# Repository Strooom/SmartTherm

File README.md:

# SmartTherm
Controlling a Junkers heating (Eurostar ZWE24) with an IoT thermostat

* schematics (kiCAD)
* PCB (kiCAD)
* TouchScreen control (Nextion display)
* SmartPhone app (Blynk)
* 3D Printed enclosure (Fusion360)
* Alternative config with ESPHome and Home Assistant

All documentation is in the Wiki : https://github.com/Strooom/SmartTherm/wiki

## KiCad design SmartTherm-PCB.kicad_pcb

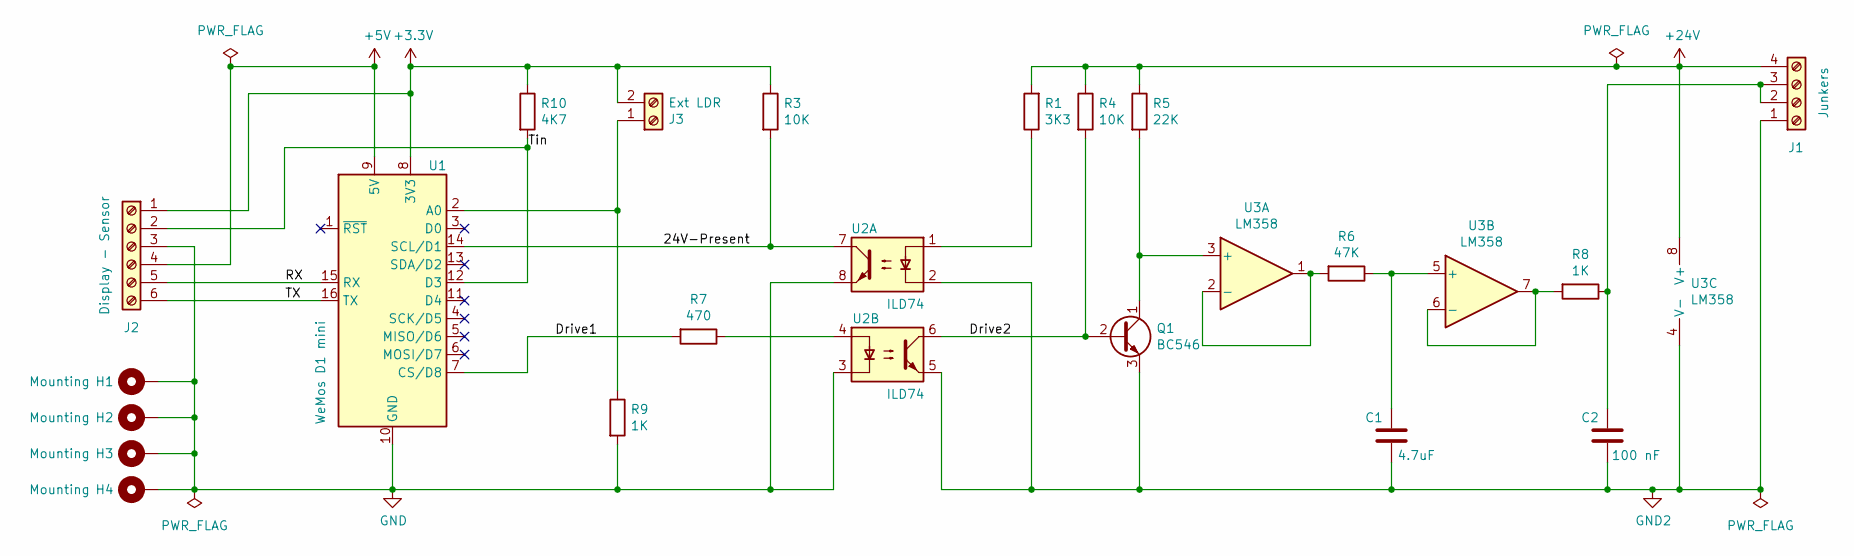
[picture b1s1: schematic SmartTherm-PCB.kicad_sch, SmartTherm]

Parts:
C1: 4.7uF; C_Disc_D4.7mm_W2.5mm_P5.00mm; manufacturerPartNumber RCEC72A475MWM1H03A; mouserPartNumber 81-RCEC72A475MWM1H3A
C2: 100 nF; C_Disc_D4.7mm_W2.5mm_P5.00mm; manufacturerPartNumber FA22X7R2J104KNU06; mouserPartNumber 810-FA22X7R2J104KNU6
H1, H2, H3, H4: Mounting; MountingHole_3.2mm_M3_Pad; manufacturerPartNumber na; mouserPartNumber na
J1: Junkers; TerminalBlock_Junkers; manufacturerPartNumber 1711042; mouserPartNumber 651-1711042
J2: Display - Sensor; TerminalBlock_Phoenix_PT-1,5-6-5.0-H_1x06_P5.00mm_Horizontal; manufacturerPartNumber 1730052; mouserPartNumber 651-1730052
J3: Ext LDR; TerminalBlock_LDR; manufacturerPartNumber 1711026; mouserPartNumber 651-1711026
Q1: BC546; TO-92L_Inline_Wide; manufacturerPartNumber BC546A; mouserPartNumber 637-BC546A
R1: 3K3; R_Axial_DIN0207_L6.3mm_D2.5mm_P10.16mm_Horizontal; manufacturerPartNumber RL07S332GB14; mouserPartNumber 71-RL07S-G-3.3K
R3, R4: 10K; R_Axial_DIN0207_L6.3mm_D2.5mm_P10.16mm_Horizontal; manufacturerPartNumber RL07S103GB14; mouserPartNumber 71-RL07S-G-10K
R5: 22K; R_Axial_DIN0207_L6.3mm_D2.5mm_P10.16mm_Horizontal; manufacturerPartNumber RL07S223GB14; mouserPartNumber 71-RL07S-G-22K
R6: 47K; R_Axial_DIN0207_L6.3mm_D2.5mm_P10.16mm_Horizontal; manufacturerPartNumber RL07S473GB14; mouserPartNumber 71-RL07S-G-47K
R7: 470; R_Axial_DIN0207_L6.3mm_D2.5mm_P10.16mm_Horizontal; manufacturerPartNumber RL07S471GB14; mouserPartNumber 71-RL07S-G-470
R8, R9: 1K; R_Axial_DIN0207_L6.3mm_D2.5mm_P10.16mm_Horizontal; manufacturerPartNumber RL07S102GB14; mouserPartNumber 71-RL07S-G-1K
R10: 4K7; R_Axial_DIN0207_L6.3mm_D2.5mm_P10.16mm_Horizontal; manufacturerPartNumber RL07S472GB14; mouserPartNumber 71-RL07S-G-4.7K
U1: WeMos D1 mini; WEMOS_D1_mini_light
U2: ILD74; DIP-8_W7.62mm; manufacturerPartNumber ILD74; mouserPartNumber 782-ILD74
U3: LM358; DIP-8_W7.62mm; manufacturerPartNumber LM358N/NOPB; mouserPartNumber 926-LM358N/NOPB

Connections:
+3.3V: J2.1, J3.2, R3.1, R10.1, U1.8 (3V3)
+5V: J2.4, U1.9 (5V)
+24V: J1.4, R1.2, R4.1, R5.1, U3.8 (V+)
/24V-Present: R3.2, U1.14 (SCL/D1), U2.7
/Drive1: R7.2, U1.7 (CS/D8)
/Drive2: Q1.2 (B), R4.2, U2.6
/RX: J2.5, U1.15 (RX)
/TX: J2.6, U1.16 (TX)
/Tin: J2.2, R10.2, U1.12 (D3)
GND: H1.1, H2.1, H3.1, H4.1, J2.3, R9.2, U1.10 (GND), U2.3, U2.8
GND2: C1.2, C2.2, J1.1, Q1.3 (E), U2.2, U2.5, U3.4 (V-)
unnamed: C2.1, J1.2, J1.3, R8.1
unnamed: J3.1, R9.1, U1.2 (A0)
unnamed: Q1.1 (C), R5.2, U3.3 (+)
unnamed: R1.1, U2.1
unnamed: R7.1, U2.4
unnamed: R6.2, U3.1, U3.2 (-)
unnamed: C1.1, R6.1, U3.5 (+)
unnamed: R8.2, U3.6 (-), U3.7

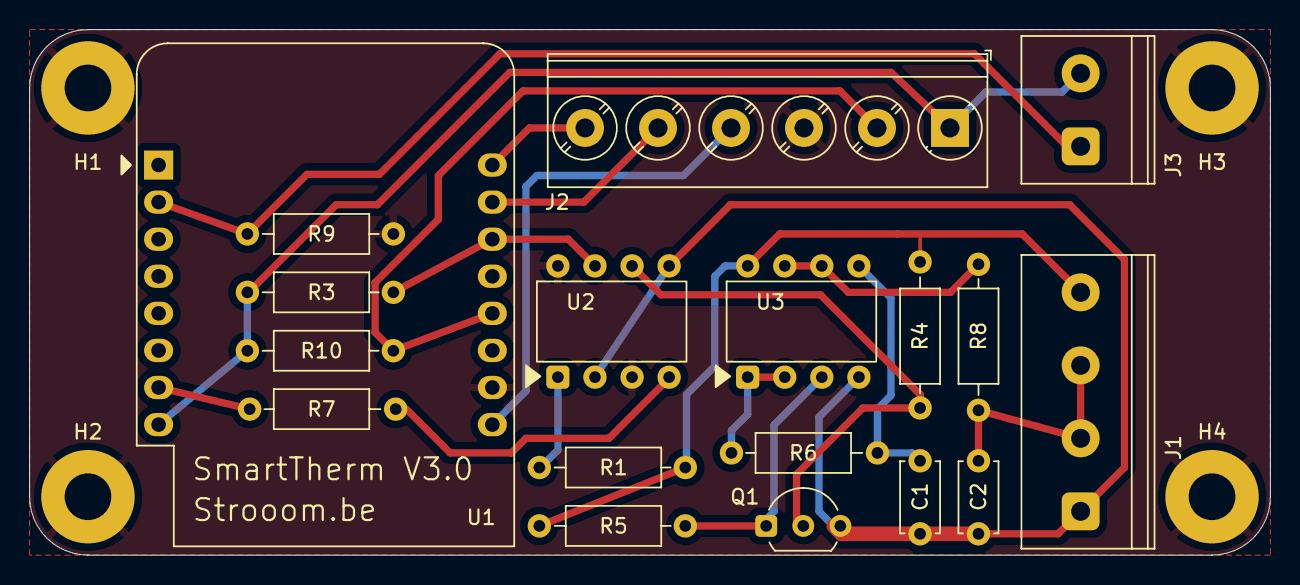
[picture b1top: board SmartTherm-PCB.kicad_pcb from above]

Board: 2 copper layers, 85.0 x 36.0 mm, 22 parts (0 on the bottom side), 19 nets.

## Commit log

2020-02-17 Completed file headers
2020-02-17 Added license file
2020-02-17 Added editor settings
2020-02-17 improved directories
2020-02-17 Added pictures
2020-04-19 Added a Nextion display
    moved OTA code from loop() to separate functions
    added a Nextion display, which for the time being is only displaying temperature and time. Reading buttons will be added later
2021-04-03 add hardware schematics and pcb
2021-04-03 adding images
2021-04-03 add scope screenshots
2023-01-28 Add gerber files and a pdf with the list of components
2023-01-28 Add esphome files
2023-02-03 Add Interactive HTML BOM components list
2023-11-13 Update for recent ESPHome releases
    - change switch restore_state to restore_mode as the former configuration option is not supported anymore
    - change `onboard_led` to be a status_led light platform, so it can be double purposed as both ESPHome Status LED and heating indicator
    - add some entity icons, device class
2023-11-13 Update api config options
    - API password is not supported anymore, it needs encryption
2024-11-26 reorganize repository for workflow
2024-11-26 update BOM
2024-11-26 updates to pass ERC/DRC
2024-11-26 add workflow generated files
2024-11-26 footprint updates
2024-11-26 remove files from template
2024-11-26 update workflow to output more fields in BOM
2024-11-27 test kibot 001
2024-11-27 test kibot 002
2024-11-27 remove template files
2024-11-27 add kicost
2024-11-27 kicost v2
2024-11-27 add update xml
2024-11-27 split large yaml file into separate file per output category
2024-11-27 split yaml
2024-11-27 split number two
2025-02-04 testing field check
2025-02-04 test 2
2025-02-04 test case sensitive
2025-02-04 test missing fields
2025-02-04 test regex
2025-02-04 further tests
